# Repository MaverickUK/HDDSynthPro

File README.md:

# IDE Synth Bay

An RP2350 that pretends to be an IDE hard disk and CD-ROM drive, as the base for a future HDD Synth that *is* the drive rather than one that listens to it.

At this stage it is a proof of concept on an Olimex RP2350-PICO2-BB48. It is tested through a USB-IDE adapter from macOS and Windows, and in real retro PCs (see [Testing](#testing)). See [docs/plan.md](docs/plan.md) for the slices and [docs/wiring.md](docs/wiring.md) for the connections. For an interactive wiring diagram, open [docs/wiring.html](docs/wiring.html) in a browser. [docs/bringup.md](docs/bringup.md) is the checklist for hardware day. [docs/pcb-bom.md](docs/pcb-bom.md) sketches the custom PCB that follows the prototype. [docs/activity.md](docs/activity.md) explains how the drive tells sequential from random activity, for more realistic sounds.

Formerly HDD Synth Pro: renamed IDE Synth Bay once it served CD-ROM drives as well as hard disks. The repository, file names and the firmware's own messages keep the old name.

The logo? "BAY" is meant to be an IDE cable, with pin 1 being red :)

<br clear="left">

## Contents

- [Prototyping](#prototyping)
- [Status](#status)
- [Testing](#testing)
  - [Machines](#machines)
  - [Speeds](#speeds)
  - [The benchmark image](#the-benchmark-image)
- [Quick start](#quick-start)
- [Licence](#licence)

## Prototyping

Currently I'm creating a proof of concept on a BB48 dev board that exposes all of the GPIO lines of the RP2350 chip so that I'm able to hook them up to the IDE bus.

Which means it's possible to create an emulated IDE drive mounted on an SD card.

I'm not yet sure if this will exist alongside the original HDD Synth or will supersede it, time will tell

## Status

The drive works as a read/write IDE hard disk (and, exploratory, a CD-ROM drive), serving disk images from a microSD card, on the Olimex BB48 and on the IDE Synth Bay PCB (rev 0.3). It has run four retro PCs and soaked for 10 hours at a time behind a USB-IDE adapter. Releases are tagged on `main` with the firmware files (`v0.31.0`: on the PCB the card runs over 4-bit SDIO).

- **The drive build** (`pio run -e bb48_drive`) serves `HDDSYNTH.IMG` from a microSD card, or whichever image `HDDSYNTH.INI` names ([docs/settings.md](docs/settings.md)). Without a card it serves a 64 MB welcome disk, with writes kept in RAM until reboot.
- **Transfer modes:** PIO modes 0-3 and multiword DMA mode 2. Every register's value is ready as soon as it's addressed (early answers, on by default since 0.27.0), so controllers that ignore IORDY work too, and IORDY is let go after 23 µs with no strobe, which keeps 16-bit ISA cards safe; they also get IOCS16#. Experimental, on branch `register-table`: the register table (`register_table = on`, [docs/register-table.md](docs/register-table.md)), where the drive's PIO answers every register read itself within about 30 ns, so no read waits for its processor; the fastest PIO through USB adapters yet, not yet tried on retro PCs.
- **Few settings needed:** the drive takes its CHS geometry from the image's own partition table (an image from an old drive boots with the BIOS on auto), and an image over 4 GB can be split across files on a FAT32 card (`tools/split_image.py`; 0.28.0, not yet tried on hardware). `HDDSYNTH.INI` mostly just names the image.
- **Checked on the cable:** the drive watches its own bus, and checks every data word the host takes off it against what it meant to send.
- **The board's LED** lights for drive activity, as a hard disk's would.
- **Next:** the register table on retro PCs, then into a release; PCB rev 0.4 (ordered 10 Nov: IOCS16# for ISA cards, PSRAM, CD audio); the activity link to the HDD Synth ([docs/activity-link.md](docs/activity-link.md)).

The listen-only build (`pio run -e bb48`) records every IDE register access it sees without driving any pin, for studying what a host does.

## Testing

### Machines

| Machine | IDE controller | Mode used | Firmware | What ran | Result |
|---|---|---|---|---|---|
| USB-IDE adapter (Norelsys NS1081; JMicron ID on Windows), from macOS and Windows | Adapter's own | PIO 0-3, multiword DMA 2 | 0.16-0.18 | Detection and re-detection, partitioning and formatting, the rig tests (slices 0-5), standby and wake, FLUSH CACHE, a card pulled and put back, soaks | 10-hour soaks clean in PIO mode 3 (28.9 GB, 49.5 million sectors checked on the cable, 0 bad) and in DMA (51.9 GB, 89.0 million sectors, 0 bad) |
| ICL HRA 386 (BIOS 1.20, 1992) | 16-bit ISA IDE card | PIO 0 (the card's ISA timing) | 0.22.0, 0.23.15 | Boots MS-DOS 5 from a copy of its own CF card; CHKDSK, copying files. The benchmark image: `HDDBENCH` and a 14-minute soak | Works: the benchmark passed, and the soak checked about 400 MB with 0 bad sectors. Needs the IOCS16# wire (IDE pin 32 to GPIO 2); since 0.27.0 no settings (it boots on the defaults) |
| Pentium 200 (Intel PIIX, Phoenix BIOS) | PIIX, on the motherboard | PIO 3 (no DMA offered yet) | 0.23.15 | Boots Windows 95 from a copy of its own 4 GB CF card, with Windows' own 32-bit disk driver (`ESDI_506.PDR`) | Works. 163,847 sectors checked on the cable, 0 bad. Needs `early_answers = on`: in its BIOS's timing the PIIX ignores IORDY ([docs/no-iordy.md](docs/no-iordy.md)) |
| Evesham, on the IDE Synth Bay PCB | On the motherboard | PIO 3 | 0.31.0 (`pcb_drive`, `bb48_hdcd`) | The benchmark image over SDIO, on early answers and on the data lane, and a 15-minute soak; Doom from the CD-ROM (device 1) beside the 386's disk | Works: 2.39 million sectors checked on the cable in the soak, 0 bad; no read the PC didn't wait for, the CD's included (the BB48 had 26 on 4 Nov) |
| Evesham, AMD Athlon XP 2000+, 1 GB, GeForce 2 GTS | On the motherboard | PIO 3 | 0.25.0-0.26.1 | Booted the benchmark image first time (`HDDBENCH`). Booted the ICL 386's MS-DOS 5 disk with the BIOS on auto, using `geometry = 756/13/51` (that drive's own geometry); ran Duke Nukem | Works: the benchmark passed, with 47,423 sectors checked on the cable and 0 bad. Needs `early_answers = on`: it didn't wait for IORDY on 115 reads under DOS |

What each machine needed, and the dead ends, are in [CHANGELOG.md](CHANGELOG.md) (0.19-0.23) and [docs/retro-test.md](docs/retro-test.md).

### Speeds

Measured from the host, in MB/s:

| Host | Disk | Mode | Read | Write |
|---|---|---|---|---|
| USB-IDE adapter | built-in test disk (RAM) | PIO 3 | 1.36 | 1.79 |
| USB-IDE adapter | built-in test disk (RAM) | Multiword DMA 2 | 7.70 (1,100 random 4 KB reads/s) | 13.9 |
| USB-IDE adapter | SD card image (SPI) | PIO 0 | 1.31 | 1.61 (write-behind on), 0.94 (off) |
| USB-IDE adapter | SD card image (SPI) | PIO 3 | not measured | 1.65 (write-behind on), 1.05 (off) |
| USB-IDE adapter | SD card image (SPI) | Multiword DMA 2 | not measured | 2.23 (write-behind on) |
| ICL 386 (`DOSBENCH.IMG`, through the BIOS) | SD card image | PIO 0 | 1.51 (random: 1.09 ms a read) | 0.72 |
| Pentium 200 | SD card image | PIO 3 | not measured yet | not measured yet |
| Evesham Athlon XP 2000+ (`DOSBENCH.IMG`, through the BIOS) | SD card image | PIO 3 | 1.81 (random: 0.98 ms a read) | 1.28 |
| USB-IDE adapter, the PCB | SD card image (SDIO) | PIO 3 | 1.20 | 1.02 |
| USB-IDE adapter, the PCB | SD card image (SDIO) | Multiword DMA 2 | 6.2-6.6 (about 680 random 4 KB reads/s) | 5.8-7.2 |
| Evesham, the PCB (`DOSBENCH.IMG`) | SD card image (SDIO) | PIO 3, early answers | 2.29 (random: 0.98 ms) | 1.25 |
| Evesham, the PCB (`DOSBENCH.IMG`) | SD card image (SDIO) | PIO 3, data lane | **4.24** (random: 0.76 ms) | 2.03 |

**Limits on these figures:**
- In PIO the adapter paces itself (about 1.1 µs a word, and 10 ms before each READ), so faster PIO modes can't speed it up; DMA avoids both.
- The SD card over SPI caps image transfers at about 2 MB/s, whatever the mode; the PCB's SDIO lifts it to about 7. The Athlon's 1.81 MB/s reads on the BB48 were at the SPI limit; on the PCB, on the data lane, they're 4.24.
- The retro PCs' figures come from the benchmark image (below), through the BIOS as DOS uses the disk. The Pentium's run was cut short when its power supply failed, which was unrelated to the drive.

Every step is in [docs/speed-log.md](docs/speed-log.md).

### The benchmark image

[tools/bench-image](tools/bench-image) builds `DOSBENCH.IMG`, a 128 MB disk that boots FreeDOS and runs `HDDBENCH`:
- sequential reads and writes, and random reads, all through the BIOS;
- checks of every sector it reads against a known pattern;
- a soak that runs until a key is pressed.

Each run does the same operations on every machine, so results compare directly between machines. It runs on a 386 or later.

## Quick start

```sh
test/run_native_tests.sh                 # C++ unit tests (no hardware)
cd host && python3 -m venv .venv && .venv/bin/pip install -r requirements.txt
.venv/bin/pytest -m sim                  # simulator and parser tests (no hardware)

pio run -e bb48_drive -t upload          # build and flash the drive
pio run -t upload                        # or the listen-only build
pio device monitor                       # h help, p pin levels, s stats, S SD card

PIO_ENV=bb48_drive scripts/rig.sh -m slice3   # tests, build, flash, rig test
```

Read the power-order rule in [docs/wiring.md](docs/wiring.md) before connecting the adapter. The SD card's wiring is in [docs/wiring-sd.html](docs/wiring-sd.html).

## Licence

IDE Synth Bay is free software, under the GNU General Public License, version 3 ([LICENSE](LICENSE)), as is [HDD Synth](https://github.com/MaverickUK/HDDSynth_Native). You can use, study, change and share it; if you share a changed version, it must be under the same licence, with its source.

The benchmark image's build downloads [FreeDOS](https://www.freedos.org/), which is GPL too; FreeDOS isn't stored in this repository.

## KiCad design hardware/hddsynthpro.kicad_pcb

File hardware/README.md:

# IDE Synth Bay hardware

The KiCad project for the IDE Synth Bay board (formerly HDD Synth Pro): an RP2350B that acts as an IDE drive. The files keep the old name (`hddsynthpro.kicad_*`, the `HDDSynthPro` library). The microcontroller and its support parts (core regulator, crystal, flash, USB) are on the board, following Raspberry Pi's RP2350 minimal design; rev 0.1 used a Pimoroni PGA2350 module instead. The design and the reasons for it are in [docs/pcb.html](../docs/pcb.html); open it in a browser.

Status: **rev 0.4, ordered 10 Nov 2026**; `production/` holds the files sent. Rev 0.3 (ordered 28 Oct) is in `production/` and in git history (commit 4fee041). What rev 0.4 adds, and why: [docs/pcb-rev04.md](../docs/pcb-rev04.md).

## Rev 0.4: where it stands

- **Pin 20 (9 Nov):** J5 and J7 use copies of KiCad's footprints with pin 20 as an unplated hole (`make_footprints.py`), since no stocked header leaves it out; rev 0.3's had to be cut. KiCad drops an unplated hole's pin number, so DRC's schematic check gives two expected `net_conflict` warnings, "No pad found for pin 20" on J5 and J7.
- **Solder mask (12 Nov):** the RP2350B (U1) and the USB-C socket (J1) use copies of KiCad's footprints (`make_footprints.py`) with one mask opening per row of fine-pitch pads. Their pads are 0.2 mm apart, and PCBWay can't make a strip of black mask narrower than 0.22 mm between pads, so it asked whether to leave those strips out. For rev 0.4's order the answer was to leave them out on U1 and keep the black. The narrowest strip left on the board is 0.25 mm (the bus switches). The files in `production/` are still the ones sent, without this change.
- **Done:** the schematic (ERC: 0 errors, 0 warnings; `check_netlist.py` passes, and was checked to fail on a wrong pin), the Molex footprint, the placement and the routing (Freerouting 2.5.0 on Windows, then `tools/widen_power.py`). DRC with `--schematic-parity`: 0 unconnected pads, 0 differences from the schematic, only rev 0.3's two expected USB-C silkscreen warnings.
- **VB, the 5 V supply:** Freerouting ignores the Power class's 0.6 mm, so `layout_pcb.py` lays VB's two long branches (D6, Molex, up the right side; D7, 44-pin, along the bottom edge) 0.6 mm wide and locked before routing: about 0.08 ohm, 16 mV at 200 mA. The run along the top (D5, D1, C1, D2) is the router's, widened to mostly 0.3-0.5 mm (about 19 mm at 0.15-0.2 mm near pads; about 0.13 ohm from USB). Fixing that run too was tried three ways (8 Nov): each crowded the PSRAM and flash's QSPI lines, the board's tightest spot, and left one or two of them unrouted.
- **Worth a look in review:** SD_VDD (mostly 0.2-0.4 mm), and the chip side's detours, as on rev 0.3.
- **Before ordering:** a day with rev 0.3 ([pcb-bringup.md](../docs/pcb-bringup.md)) to choose the series resistors and confirm SDIO; check J8's and J9's footprints against real parts (no LCSC part found for J8); pull pin 20 (IDE's key) out of J5 and J7 with pliers after assembly (it's in an unplated hole, ringed on the silkscreen, so it isn't soldered); check J7's rotation in JLCPCB's preview (its `FT Rotation Offset` is copied from the 40-pin header's, unchecked).
- **Not yet updated for rev 0.4:** [docs/pcb.html](../docs/pcb.html), the interactive design page, and `tools/jlcpcb.py`'s `JLC_FIX` table.

## Files

| File | What |
|---|---|
| `hddsynthpro.kicad_pro` | The project: open this in KiCad (9 or 10) |
| `hddsynthpro.kicad_dru` | One custom design rule: 0.125 mm spacing inside Raspberry Pi's regulator layout only |
| `hddsynthpro.kicad_sch` | Root sheet, with one sheet per block |
| `power.kicad_sch` | USB-C, the 5 V header, the link's 5 V input, (rev 0.4) the Molex and 44-pin 5 V inputs, diode-OR, the AMS1117 3.3 V regulator, ESD, BOOTSEL/RESET, SWD |
| `mcu.kicad_sch` | The RP2350B and its support circuit, (rev 0.4) the PSRAM, the activity link socket (J3) and the LEDs |
| `ide.kicad_sch` | The four SN74CB3T3245 bus switches, the series-resistor footprints, the 40-pin and (rev 0.4) 44-pin IDE headers |
| `sd.kicad_sch` | The microSD socket, its pull-ups and (rev 0.4) its power switch |
| `audio.kicad_sch` | Rev 0.4's CD audio out: PWM, RC filters and the 4-pin header |
| `hddsynthpro.kicad_pcb` | The board: 100.33 × 69.88 mm, the HDD Synth Mk5's outline and M3 holes, 4 layers (signals, GND plane, 3V3 plane, signals) |
| `HDDSynthPro.kicad_sym`, `HDDSynthPro.pretty/` | Parts KiCad lacks: the SN74CB3T3245's symbol (pinout from TI's datasheet); Raspberry Pi's polarity-marked inductor and wide-pad 0402 footprints; the TF PUSH microSD socket; the RP2350B's QFN-80 and the USB-C socket with one mask opening per row of pads; the logo and the easter eggs. (The old PGA2350 symbol and footprint stay for reference.) |
| `tools/gen_schematic.py` | Generated the schematic, with an LCSC part number and any Fabrication Toolkit offsets on every part |
| `tools/layout_pcb.py` | Placed the parts and laid the fixed copper (run with KiCad's own Python) |
| `tools/make_footprints.py` | Made the inductor, wide 0402, TF PUSH, (rev 0.4) Molex disk-power, pin-20-unplated IDE header and one-mask-opening QFN-80 and USB-C footprints |
| `tools/make_logo.py` | Makes the silkscreen logo footprint from `media/IDESynthBay.png` |
| `tools/make_eggs.py` | Makes the easter eggs on the back (silkscreen footprints) from `media/Defrag.png` and `media/ParkHeads.png` |
| `tools/autoroute.py` | Routed the rest with Freerouting |
| `tools/jlcpcb.py` | Writes `fab/bom-jlcpcb.csv` and `fab/cpl-jlcpcb.csv` for JLCPCB's assembly service |
| `tools/check_netlist.py` | Checks the schematic against `src/config.h` and Raspberry Pi's support circuit |

Parts connect through net labels, not drawn wires: a label on a pin's short wire joins every other label of the same name on that sheet, and a global label (the arrow-shaped ones) joins its name across all sheets. GND and +3V3 are power symbols, which are global too.

## Checking it

```sh
cd hardware
kicad-cli sch erc hddsynthpro.kicad_sch                      # electrical rules: 0 violations
python3 tools/check_netlist.py                               # GPIO map and RP2350 support circuit
kicad-cli pcb drc --schematic-parity hddsynthpro.kicad_pcb   # 0 errors, 0 unconnected, 0 parity issues
$KICAD_PYTHON tools/check_mask_webs.py hddsynthpro.kicad_pcb  # no solder mask strip under 0.22 mm (KiCad's Python)
```

On Windows (KiCad 10 in `C:\Program Files\KiCad\10.0`), from Git Bash: put `/c/Program Files/KiCad/10.0/bin` on `PATH`, set `KICAD_SHARE="C:/Program Files/KiCad/10.0/share/kicad"` for `gen_schematic.py`, and run `layout_pcb.py` with that folder's `python.exe`. `gen_schematic.py` reproduces the committed schematic byte for byte there.

`check_netlist.py` exports the netlist with `kicad-cli` and follows each IDE signal from its GPIO, through the 33 Ω resistor where there is one and the bus switch, to the IDE header, and checks it lands on the ATA pin. It also checks the microSD socket, the link, the LED, the bus-switch enable, the IDE grounds, and the RP2350B's support circuit against Raspberry Pi's design: every supply pin's rail, the inductor's polarity, the VREG_AVDD filter, the crystal and its 1 kΩ, the flash wiring and the USB 27 Ω resistors. Run it after every schematic edit: CLAUDE.md requires the pin map to agree everywhere. (DRC's two remaining warnings are the USB-C socket's outline overhanging the board edge, as it's meant to.)

## The board

The outline (100.33 × 69.88 mm, 2.54 mm corner radius) and the four M3 holes are the HDD Synth Mk5's, so the two boards stack on standoffs. The holes sit 9.76 mm in from the left edge, 13.97 mm from the right and 4.09 mm from the top and bottom.

The 40-pin IDE header runs down the left side, pin 1 at the top, just inside the left-hand holes (its shroud is too long to fit between them). The four bus switches (SN74CB3T3245, 8 channels each) sit in a column beside it, IDE side (B, pins 11-18) facing it, each with its 100 nF below it. Each takes eight consecutive header signals in pin order, so those traces run straight: U2 RESET# and DD4-DD10, U3 DD0-DD3 and DD11-DD14, U5 DD15, the strobes, IORDY, INTRQ, DMA and DA1, U6 DA0, DA2 and the chip selects (four spare channels).

The RP2350B (QFN-80) is in the middle, its data pins (left side) facing the switches. The GPIO numbers are the PGA2350's, so the firmware's pin map is unchanged. Around it:
- **Above:** Raspberry Pi's core regulator (the polarity-marked 3.3 µH inductor, 4.7 µF caps, 33 Ω/4.7 µF filter), the USB 27 Ω resistors and the QSPI flash, all placed and laid out exactly as on their RP2350A minimal board, whose pins sit in the same places relative to the regulator.
- **Below:** the 12 MHz crystal with its 15 pF caps and 1 kΩ.
- **Under the chip:** each supply pin has a short stub to its own via (3V3 to the 3V3 plane, 1V1 to a bottom-layer track joining the DVDD pins to the regulator), leaving the outward lanes for signals.

USB-C, the 5 V input, the link socket and the SWD header are along the top edge, with the AMS1117 by the power parts; the microSD socket is on the right edge, card in from the right, with its pull-ups beside it; the buttons are at the bottom right, and the logo at the bottom, under the chip.

Design rules are set for a 4-layer board at JLCPCB-class fabs: 0.2 mm tracks and 0.15 mm clearance by default, 0.6 mm for the `Power` net class (VB, VBUS_USB, 5V_EXT, 5V_LINK), 0.6/0.3 mm vias (0.5/0.3 for the fixed ones). Project rules that differ from KiCad's defaults: minimum track 0.1 mm (Freerouting necks some traces to 0.12 mm between pads), minimum clearance 0.12 mm with 0.125 mm allowed only inside the `RP2350 core` area (Raspberry Pi's layout), minimum drill 0.2 mm (the QFN's thermal vias), and one thermal spoke enough on the outer GND pours.

### Routing

Some copper is laid by `layout_pcb.py` and locked, so the router works round it:
- Raspberry Pi's regulator fills, tracks and vias, and their QSPI fan-out to the flash;
- the supply stubs and vias under the RP2350B, and the 1V1 track joining the DVDD pins;
- USB D+/D- from the 27 Ω resistors through U4 to both rows of USB-C contacts (the inner contacts cross over on the bottom layer), and VBUS.

The rest is autorouted with Freerouting 2.5.0 (the Java build; the native CLI crashed). `autoroute.py` first gives every other surface-mount GND and +3V3 pad a short stub and via to its plane, passes the inner layers to Freerouting as planes so it never routes on them, then removes dangling tracks and vias and pours GND on both outer layers.

What to look at when reviewing it:
- **The IDE side is short and direct**: header to switch B pins, on the top layer.
- **The chip side is autorouter-shaped**: some runs take detours, partly on the bottom layer. Mode 0 timing doesn't mind, but shorter runs, especially for DIOR#/DIOW#/IORDY, would be better.
- **Ground return**: signals that change layer don't have a GND via beside them; the inner GND plane is under everything, which covers most of it.

To route again after moving parts (it keeps existing traces, so delete the ones you want rerouted): get the Freerouting jar and a Java 25 runtime (Eclipse Temurin; on Windows `winget install EclipseAdoptium.Temurin.25.JRE`), then

```sh
FREEROUTING=freerouting-2.5.0.jar JAVA=.../bin/java \
  /Applications/KiCad/KiCad.app/Contents/Frameworks/Python.framework/Versions/Current/bin/python3 tools/autoroute.py
kicad-cli pcb drc --refill-zones --save-board --schematic-parity hddsynthpro.kicad_pcb
```

Then `tools/widen_power.py` (KiCad's Python, `kicad-cli` on `PATH`) widens VB to 0.6 mm and SD_VDD to 0.4 mm wherever the clearances allow, stepping each segment down until DRC is clean: Freerouting doesn't keep the Power class's width.

The logo (17.2 × 15 mm, bottom middle of the front) is the board-only footprint `LOGO_IDESynthBay`: dark pixels of `media/IDESynthBay.png` as silkscreen (the discs' grey shading drops out), "BAY"'s thin bars closed into solid letters, strokes widened so they print. The easter eggs on the back come the same way from `tools/make_eggs.py`. `tools/layout_pcb.py --silkscreen hddsynthpro.kicad_pcb` redoes the logo, the easter eggs and the labels on the routed board without touching the traces; `--fields` copies the schematic's fields (LCSC numbers, offsets) onto it.

## Editing

The `.kicad_sch` and `.kicad_pcb` files are the source of truth once edited in KiCad. Running `gen_schematic.py` or `layout_pcb.py` again **overwrites** them (the layout loses its routing), so use them only to start over.

## Ordering assembled boards from JLCPCB

Every part carries its JLCPCB part number in an `LCSC` field, so the Fabrication Toolkit plugin's BOM has them. Parts whose JLCPCB footprint is turned or centred differently from KiCad's also carry `FT Rotation Offset` / `FT Position Offset` fields, so the plugin's placement file is right too. These were found by fitting JLCPCB's own footprints onto KiCad's.

`python3 tools/jlcpcb.py` writes the same BOM and placement files independently (its `JLC_FIX` table holds the same corrections). On 27 Oct 2026 the parts for 5 boards came to about $68.50 at JLCPCB, with 13 extended (setup-fee) lines; the bus switches are about half of it.

- **The inductor (L1, C42411119) was out of stock** at JLCPCB on 27 Oct 2026 (6 that morning, 0 that afternoon). Raspberry Pi require this part. Buy it through JLCPCB's global sourcing or pre-order, or send your own.
- **Check rotations in JLCPCB's placement preview**, especially L1's polarity dot (at its 1.1 V end, away from the RP2350's LX pin), the TSSOP switches, the SOT-23-6, the QFN, the flash and the USB-C socket.
- **Cheaper flash:** the firmware is about 100 KB, so a 2 MB W25Q16JVSSIQ (C131025, same footprint, about $1.24) would do instead of the 16 MB W25Q128 ($2.58), if the firmware's flash size is set to match.

## Before ordering a board

- **Power from the HDD Synth.** J3's pin 1 takes 5 V through D5 (a B5819W since rev 0.4; an SS14 before) into VB, so one supply can run both boards. The Mk5's J6 pin 1 carries 3.3 V: with a Mk5, leave pin 1 of the cable unconnected (3.3 V there wouldn't damage anything, but the board would brown out on it alone). Any input works on its own; with several, the highest wins.
- **Card detect.** On generic push-push sockets the detect pin usually meets the grounded shell when a card is in (reads low with R12 pulling up); check on the first board.
- **New pins.** The board adds GP41 (`BUS_EN#`, the bus switches' enable), GP40 (card detect), GP31 and GP3 (DMARQ and DMACK#, reserved). The firmware doesn't use them yet. Until it drives GP41 low, close solder jumper JP1, or the IDE bus stays disconnected.
- **Firmware build.** The RP2350B is the PGA2350's chip with the same GPIOs, 12 MHz crystal and 16 MB flash, but it's no longer the BB48 board: the PlatformIO board for this PCB needs a generic RP2350B definition rather than `olimex_pico2bb48`.

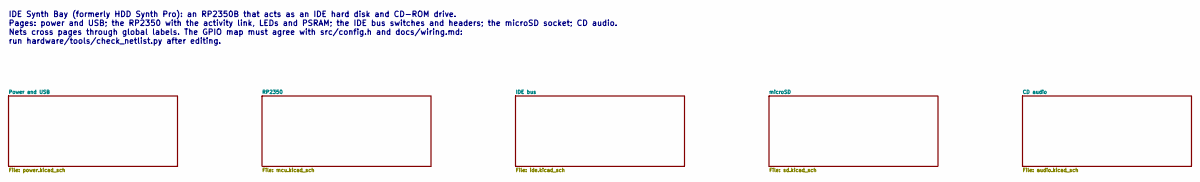
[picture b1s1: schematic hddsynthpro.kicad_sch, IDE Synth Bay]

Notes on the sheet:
IDE Synth Bay (formerly HDD Synth Pro): an RP2350B that acts as an IDE hard disk and CD-ROM drive. Pages: power and USB; the RP2350 with the activity link, LEDs and PSRAM; the IDE bus switches and headers; the microSD socket; CD audio. Nets cross pages through global labels. The GPIO map must agree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

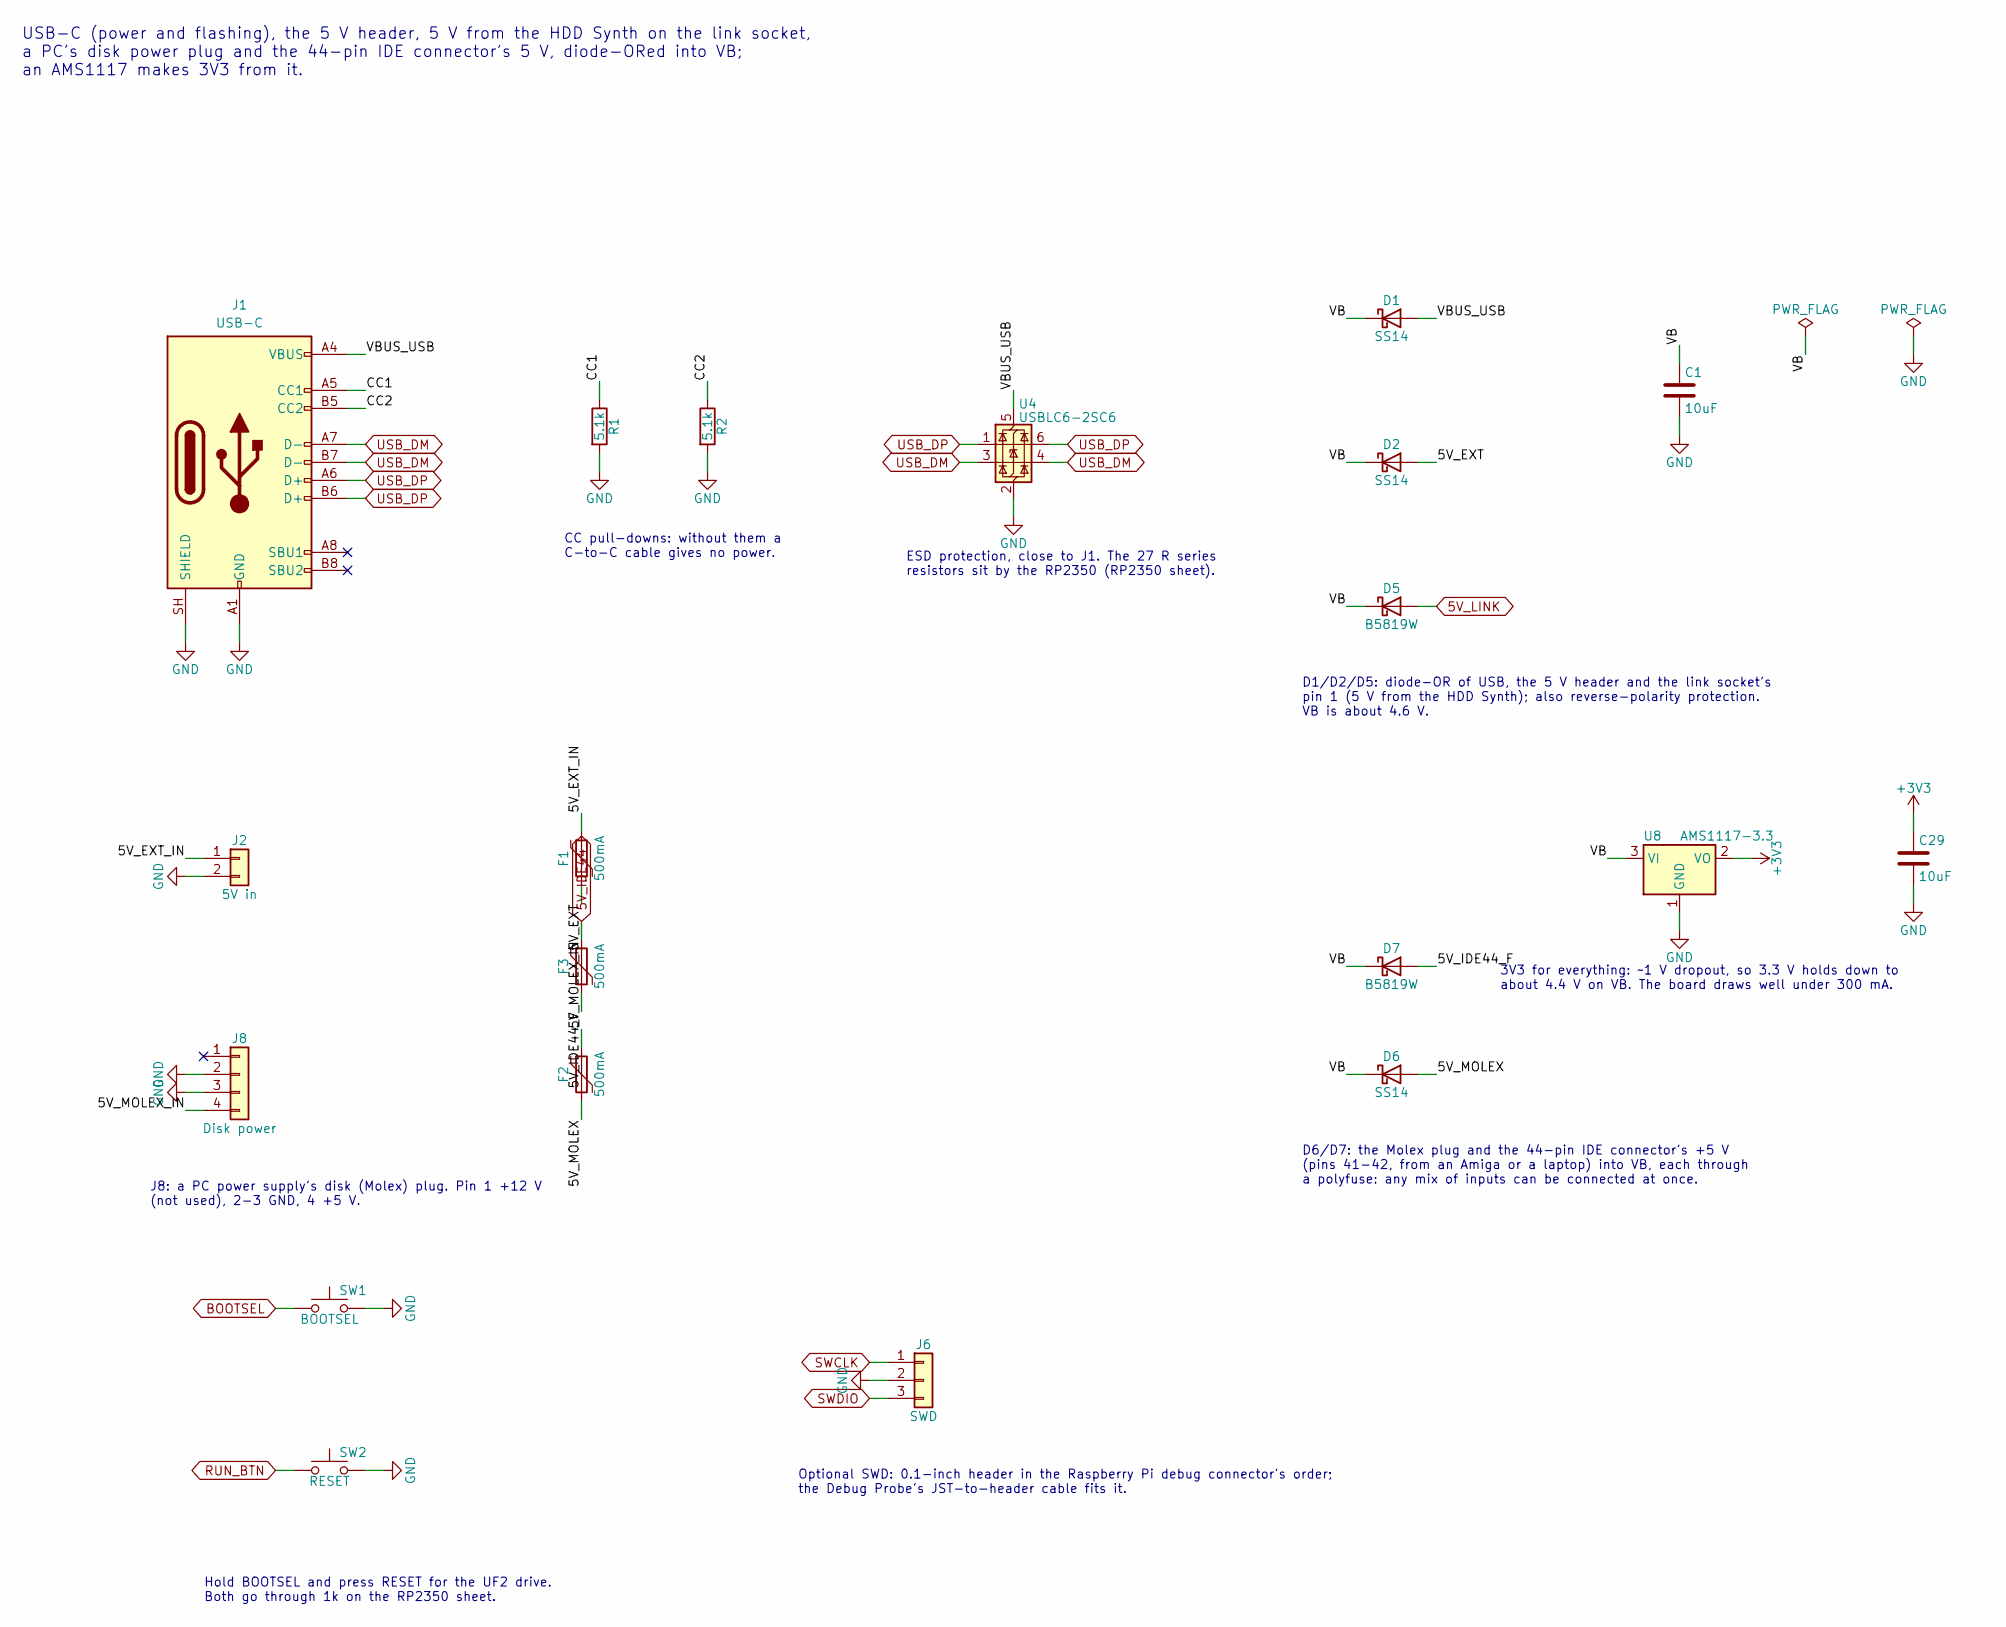
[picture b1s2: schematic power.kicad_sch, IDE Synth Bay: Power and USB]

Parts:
C1, C29: 10uF; C_0805_2012Metric; LCSC C15850
D1, D2, D6: SS14; D_SMA; LCSC C2480
D5, D7: B5819W; D_SOD-123; LCSC C8598
F1, F2, F3: 500mA; Fuse_1206_3216Metric; LCSC C19193043
J1: USB-C; USB_C_Receptacle_HRO_TYPE-C-31-M-12_OneMaskOpening; MPN HRO TYPE-C-31-M-12; LCSC C165948
J2: 5V in; JST_XH_B2B-XH-A_1x02_P2.50mm_Vertical; LCSC C158012
J6: SWD; PinHeader_1x03_P2.54mm_Vertical; LCSC C2937625
J8: Disk power; Molex_8981_1x04_P5.08mm_Vertical; MPN Molex 8981 style, 4 pins, 5.08 mm
R1, R2: 5.1k; R_0603_1608Metric; LCSC C23186
SW1: BOOTSEL; SW_Push_1P1T_XKB_TS-1187A; LCSC C318884
SW2: RESET; SW_Push_1P1T_XKB_TS-1187A; LCSC C318884
U4: USBLC6-2SC6; SOT-23-6; LCSC C2687116
U8: AMS1117-3.3; SOT-223-3_TabPin2; LCSC C6186

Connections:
5V_IDE44: F3.1; also elsewhere on the board
5V_LINK: D5.2 (A); also elsewhere on the board
+3V3: C29.1, U8.2 (VO); also elsewhere on the board
/Power and USB/5V_EXT: D2.2 (A), F1.2
/Power and USB/5V_EXT_IN: F1.1, J2.1
/Power and USB/5V_IDE44_F: D7.2 (A), F3.2
/Power and USB/5V_MOLEX: D6.2 (A), F2.2
/Power and USB/5V_MOLEX_IN: F2.1, J8.4
/Power and USB/CC1: J1.A5 (CC1), R1.1
/Power and USB/CC2: J1.B5 (CC2), R2.1
/Power and USB/VB: C1.1, D1.1 (K), D2.1 (K), D5.1 (K), D6.1 (K), D7.1 (K), U8.3 (VI)
/Power and USB/VBUS_USB: D1.2 (A), J1.A4 (VBUS), J1.A9 (VBUS), J1.B4 (VBUS), J1.B9 (VBUS), U4.5 (VBUS)
BOOTSEL: SW1.1; also elsewhere on the board
GND: C1.2, C29.2, J1.A1 (GND), J1.A12 (GND), J1.B1 (GND), J1.B12 (GND), J1.SH (SHIELD), J2.2, J6.2, J8.2, J8.3, R1.2, R2.2, SW1.2, SW2.2, U4.2 (GND), U8.1 (GND); also elsewhere on the board
RUN_BTN: SW2.1; also elsewhere on the board
SWCLK: J6.1; also elsewhere on the board
SWDIO: J6.3; also elsewhere on the board
USB_DM: J1.A7 (D-), J1.B7 (D-), U4.3 (I/O2), U4.4 (I/O2); also elsewhere on the board
USB_DP: J1.A6 (D+), J1.B6 (D+), U4.1 (I/O1), U4.6 (I/O1); also elsewhere on the board

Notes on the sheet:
USB-C (power and flashing), the 5 V header, 5 V from the HDD Synth on the link socket, a PC's disk power plug and the 44-pin IDE connector's 5 V, diode-ORed into VB; an AMS1117 makes 3V3 from it.
CC pull-downs: without them a C-to-C cable gives no power.
ESD protection, close to J1. The 27 R series resistors sit by the RP2350 (RP2350 sheet).
D1/D2/D5: diode-OR of USB, the 5 V header and the link socket's pin 1 (5 V from the HDD Synth); also reverse-polarity protection. VB is about 4.6 V.
J8: a PC power supply's disk (Molex) plug. Pin 1 +12 V (not used), 2-3 GND, 4 +5 V.
D6/D7: the Molex plug and the 44-pin IDE connector's +5 V (pins 41-42, from an Amiga or a laptop) into VB, each through a polyfuse: any mix of inputs can be connected at once.
3V3 for everything: ~1 V dropout, so 3.3 V holds down to about 4.4 V on VB. The board draws well under 300 mA.
Hold BOOTSEL and press RESET for the UF2 drive. Both go through 1k on the RP2350 sheet.
Optional SWD: 0.1-inch header in the Raspberry Pi debug connector's order; the Debug Probe's JST-to-header cable fits it.

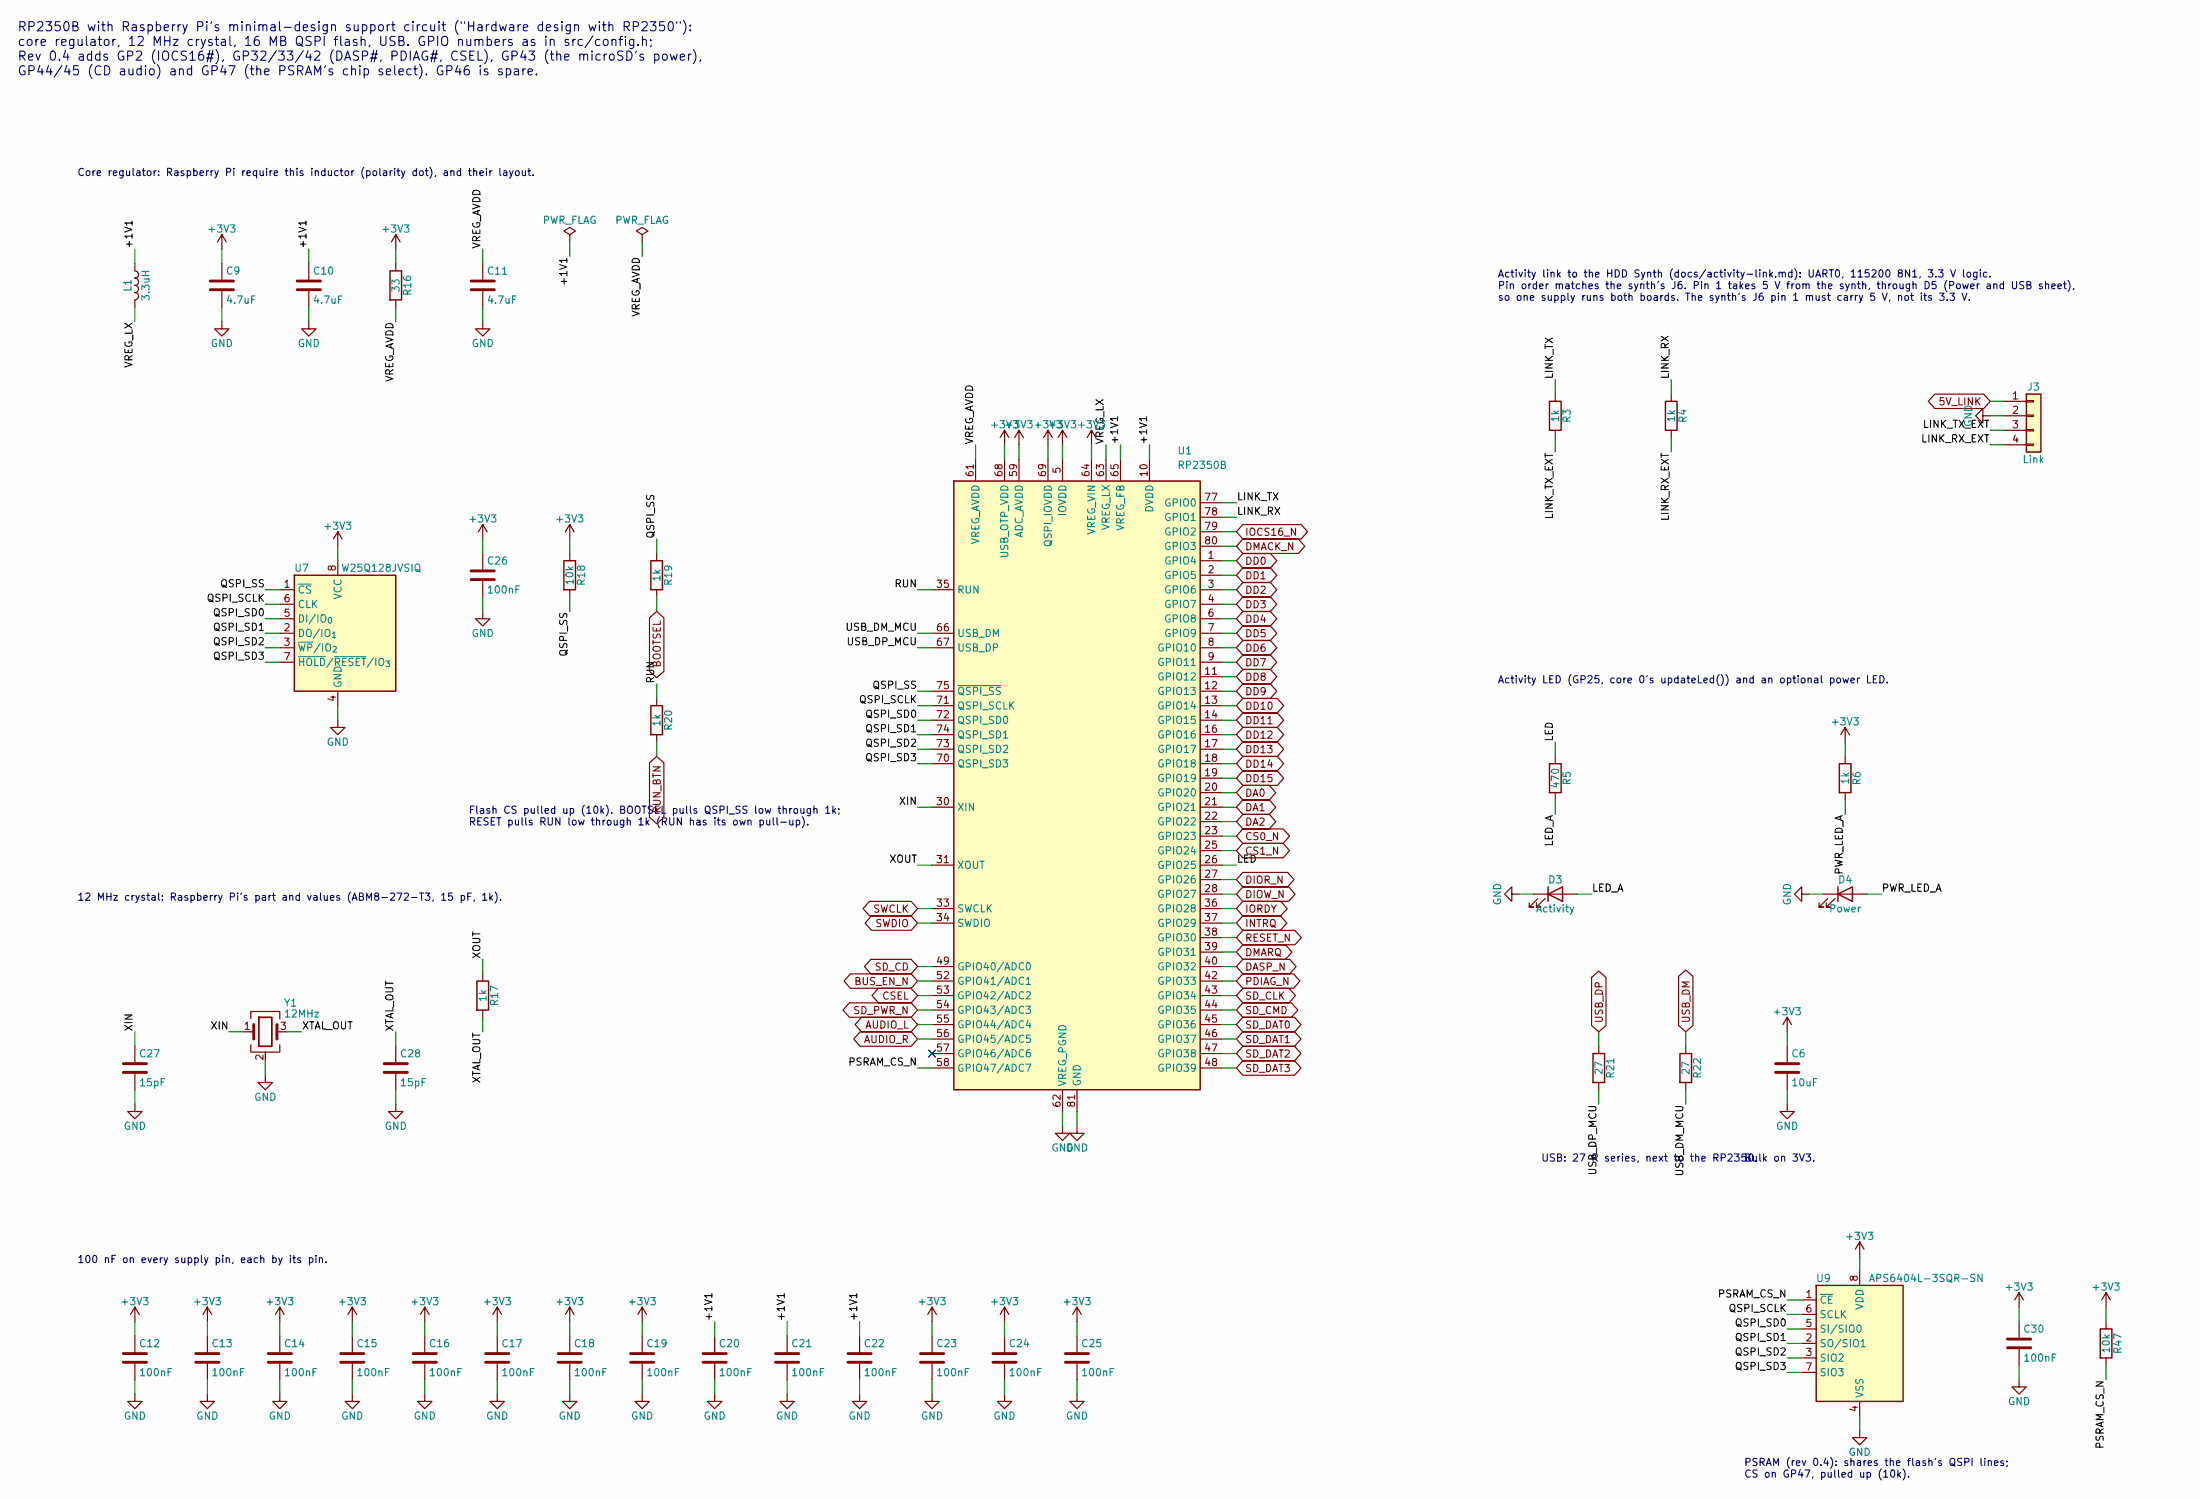
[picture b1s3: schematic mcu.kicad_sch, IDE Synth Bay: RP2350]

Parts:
C6: 10uF; C_0805_2012Metric; LCSC C15850
C9, C10: 4.7uF; C_0402_1005Metric_RPi_Wide; LCSC C23733
C11: 4.7uF; C_0402_1005Metric; LCSC C23733
C12, C13, C14, C15, C16, C17, C18, C19, C20, C21, C22, C23, C24, C25, C26, C30: 100nF; C_0402_1005Metric; LCSC C1525
C27, C28: 15pF; C_0402_1005Metric; LCSC C1548
D3: Activity; LED_0805_2012Metric; LCSC C2297
D4: Power; LED_0805_2012Metric; LCSC C84256
J3: Link; PinSocket_1x04_P2.54mm_Vertical; LCSC C2718488
L1: 3.3uH; L_Abracon_AOTA-B201610S3R3; MPN Abracon AOTA-B201610S3R3-101-T; LCSC C42411119
R3, R4, R6, R20: 1k; R_0603_1608Metric; LCSC C21190
R5: 470; R_0603_1608Metric; LCSC C23179
R16: 33; R_0402_1005Metric; LCSC C25105
R17, R19: 1k; R_0402_1005Metric; LCSC C11702
R18, R47: 10k; R_0402_1005Metric; LCSC C25744
R21, R22: 27; R_0402_1005Metric; LCSC C25100
U1: RP2350B; QFN-80-1EP_10x10mm_P0.4mm_EP3.4x3.4mm_ThermalVias_OneMaskOp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; LCSC C42415655
U7: W25Q128JVSIQ; SOIC-8_5.3x5.3mm_P1.27mm; LCSC C97521
U9: APS6404L-3SQR-SN; SOIC-8_3.9x4.9mm_P1.27mm; LCSC C5333729
Y1: 12MHz; Crystal_SMD_3225-4Pin_3.2x2.5mm; MPN Abracon ABM8-272-T3; LCSC C20625731

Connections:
5V_LINK: J3.1; also elsewhere on the board
+3V3: C6.1, C9.1, C12.1, C13.1, C14.1, C15.1, C16.1, C17.1, C18.1, C19.1, C23.1, C24.1, C25.1, C26.1, C30.1, R6.1, R16.1, R18.1, R47.1, U1.5 (IOVDD), U1.15 (IOVDD), U1.24 (IOVDD), U1.29 (IOVDD), U1.41 (IOVDD), U1.50 (IOVDD), U1.59 (ADC_AVDD), U1.60 (IOVDD), U1.64 (VREG_VIN), U1.68 (USB_OTP_VDD), U1.69 (QSPI_IOVDD), U1.76 (IOVDD), U7.8 (VCC), U9.8 (VDD); also elsewhere on the board
/RP2350/+1V1: C10.1, C20.1, C21.1, C22.1, L1.1, U1.10 (DVDD), U1.32 (DVDD), U1.51 (DVDD), U1.65 (VREG_FB)
/RP2350/LED: R5.1, U1.26 (GPIO25)
/RP2350/LED_A: D3.2 (A), R5.2
/RP2350/LINK_RX: R4.1, U1.78 (GPIO1)
/RP2350/LINK_RX_EXT: J3.4, R4.2
/RP2350/LINK_TX: R3.1, U1.77 (GPIO0)
/RP2350/LINK_TX_EXT: J3.3, R3.2
/RP2350/PSRAM_CS_N: R47.2, U1.58 (GPIO47/ADC7), U9.1 (~CE)
/RP2350/PWR_LED_A: D4.2 (A), R6.2
/RP2350/QSPI_SCLK: U1.71 (QSPI_SCLK), U7.6 (CLK), U9.6 (SCLK)
/RP2350/QSPI_SD0: U1.72 (QSPI_SD0), U7.5 (DI/IO_{0}), U9.5 (SI/SIO0)
/RP2350/QSPI_SD1: U1.74 (QSPI_SD1), U7.2 (DO/IO_{1}), U9.2 (SO/SIO1)
/RP2350/QSPI_SD2: U1.73 (QSPI_SD2), U7.3 (~WP/IO_{2}), U9.3 (SIO2)
/RP2350/QSPI_SD3: U1.70 (QSPI_SD3), U7.7 (~HOLD/~RESET/IO_{3}), U9.7 (SIO3)
/RP2350/QSPI_SS: R18.2, R19.1, U1.75 (~QSPI_SS), U7.1 (~CS)
/RP2350/RUN: R20.1, U1.35 (RUN)
/RP2350/USB_DM_MCU: R22.2, U1.66 (USB_DM)
/RP2350/USB_DP_MCU: R21.2, U1.67 (USB_DP)
/RP2350/VREG_AVDD: C11.1, R16.2, U1.61 (VREG_AVDD)
/RP2350/VREG_LX: L1.2, U1.63 (VREG_LX)
/RP2350/XIN: C27.1, U1.30 (XIN), Y1.1
/RP2350/XOUT: R17.1, U1.31 (XOUT)
/RP2350/XTAL_OUT: C28.1, R17.2, Y1.3
AUDIO_L: U1.55 (GPIO44/ADC4); also elsewhere on the board
AUDIO_R: U1.56 (GPIO45/ADC5); also elsewhere on the board
BOOTSEL: R19.2; also elsewhere on the board
BUS_EN_N: U1.52 (GPIO41/ADC1); also elsewhere on the board
CS0_N: U1.23 (GPIO23); also elsewhere on the board
CS1_N: U1.25 (GPIO24); also elsewhere on the board
CSEL: U1.53 (GPIO42/ADC2); also elsewhere on the board
DA0: U1.20 (GPIO20); also elsewhere on the board
DA1: U1.21 (GPIO21); also elsewhere on the board
DA2: U1.22 (GPIO22); also elsewhere on the board
DASP_N: U1.40 (GPIO32); also elsewhere on the board
DD0: U1.1 (GPIO4); also elsewhere on the board
DD1: U1.2 (GPIO5); also elsewhere on the board
DD2: U1.3 (GPIO6); also elsewhere on the board
DD3: U1.4 (GPIO7); also elsewhere on the board
DD4: U1.6 (GPIO8); also elsewhere on the board
DD5: U1.7 (GPIO9); also elsewhere on the board
DD6: U1.8 (GPIO10); also elsewhere on the board
DD7: U1.9 (GPIO11); also elsewhere on the board
DD8: U1.11 (GPIO12); also elsewhere on the board
DD9: U1.12 (GPIO13); also elsewhere on the board
DD10: U1.13 (GPIO14); also elsewhere on the board
DD11: U1.14 (GPIO15); also elsewhere on the board
DD12: U1.16 (GPIO16); also elsewhere on the board
DD13: U1.17 (GPIO17); also elsewhere on the board
DD14: U1.18 (GPIO18); also elsewhere on the board
DD15: U1.19 (GPIO19); also elsewhere on the board
DIOR_N: U1.27 (GPIO26); also elsewhere on the board
DIOW_N: U1.28 (GPIO27); also elsewhere on the board
DMACK_N: U1.80 (GPIO3); also elsewhere on the board
DMARQ: U1.39 (GPIO31); also elsewhere on the board
GND: C6.2, C9.2, C10.2, C11.2, C12.2, C13.2, C14.2, C15.2, C16.2, C17.2, C18.2, C19.2, C20.2, C21.2, C22.2, C23.2, C24.2, C25.2, C26.2, C27.2, C28.2, C30.2, D3.1 (K), D4.1 (K), J3.2, U1.62 (VREG_PGND), U1.81 (GND), U7.4 (GND), U9.4 (VSS), Y1.2 (G), Y1.4 (G); also elsewhere on the board
INTRQ: U1.37 (GPIO29); also elsewhere on the board
IOCS16_N: U1.79 (GPIO2); also elsewhere on the board
IORDY: U1.36 (GPIO28); also elsewhere on the board
PDIAG_N: U1.42 (GPIO33); also elsewhere on the board
RESET_N: U1.38 (GPIO30); also elsewhere on the board
RUN_BTN: R20.2; also elsewhere on the board
SD_CD: U1.49 (GPIO40/ADC0); also elsewhere on the board
SD_CLK: U1.43 (GPIO34); also elsewhere on the board
SD_CMD: U1.44 (GPIO35); also elsewhere on the board
SD_DAT0: U1.45 (GPIO36); also elsewhere on the board
SD_DAT1: U1.46 (GPIO37); also elsewhere on the board
SD_DAT2: U1.47 (GPIO38); also elsewhere on the board
SD_DAT3: U1.48 (GPIO39); also elsewhere on the board
SD_PWR_N: U1.54 (GPIO43/ADC3); also elsewhere on the board
SWCLK: U1.33 (SWCLK); also elsewhere on the board
SWDIO: U1.34 (SWDIO); also elsewhere on the board
USB_DM: R22.1; also elsewhere on the board
USB_DP: R21.1; also elsewhere on the board

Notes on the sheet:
RP2350B with Raspberry Pi's minimal-design support circuit ("Hardware design with RP2350"): core regulator, 12 MHz crystal, 16 MB QSPI flash, USB. GPIO numbers as in src/config.h; Rev 0.4 adds GP2 (IOCS16#), GP32/33/42 (DASP#, PDIAG#, CSEL), GP43 (the microSD's power), GP44/45 (CD audio) and GP47 (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
Core regulator: Raspberry Pi require this inductor (polarity dot), and their layout.
100 nF on every supply pin, each by its pin.
12 MHz crystal: Raspberry Pi's part and values (ABM8-272-T3, 15 pF, 1k).
PSRAM (rev 0.4): shares the flash's QSPI lines; CS on GP47, pulled up (10k).
Flash CS pulled up (10k). BOOTSEL pulls QSPI_SS low through 1k; RESET pulls RUN low through 1k (RUN has its own pull-up).
USB: 27 R series, next to the RP2350.
Bulk on 3V3.
Activity link to the HDD Synth (docs/activity-link.md): UART0, 115200 8N1, 3.3 V logic. Pin order matches the synth's J6. Pin 1 takes 5 V from the synth, through D5 (Power and USB sheet), so one supply runs both boards. The synth's J6 pin 1 must carry 5 V, not its 3.3 V.
Activity LED (GP25, core 0's updateLed()) and an optional power LED.

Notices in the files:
parts and their libraries:
Abracon AOTA-B201610S3R3-101-T, 3.3 uH, 2016, polarity marked. From Raspberry Pi's RP2350 minimal design (MIT licence). Pad 1 to the 1.1 V side.
0402 capacitor with Raspberry Pi's wide pad layout (RP2350 minimal design, MIT licence).
